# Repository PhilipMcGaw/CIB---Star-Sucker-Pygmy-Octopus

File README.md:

# CIB - Star-Sucker Pygmy Octopus

Programmable load for Fans, Pumps, and Load simulation - Star-Sucker Pygmy Octopus

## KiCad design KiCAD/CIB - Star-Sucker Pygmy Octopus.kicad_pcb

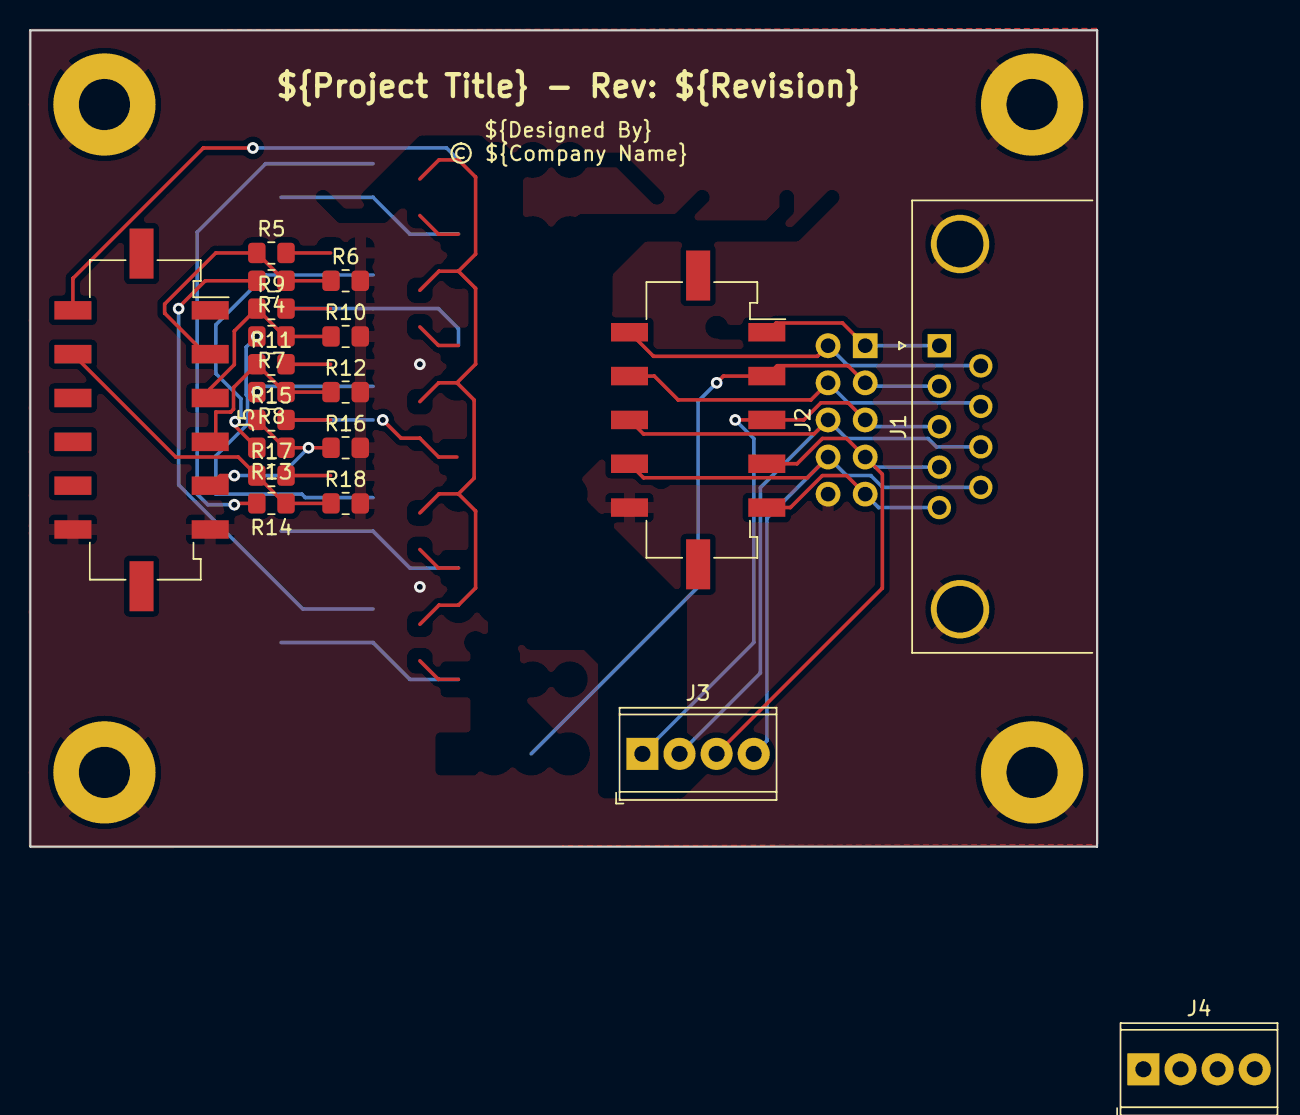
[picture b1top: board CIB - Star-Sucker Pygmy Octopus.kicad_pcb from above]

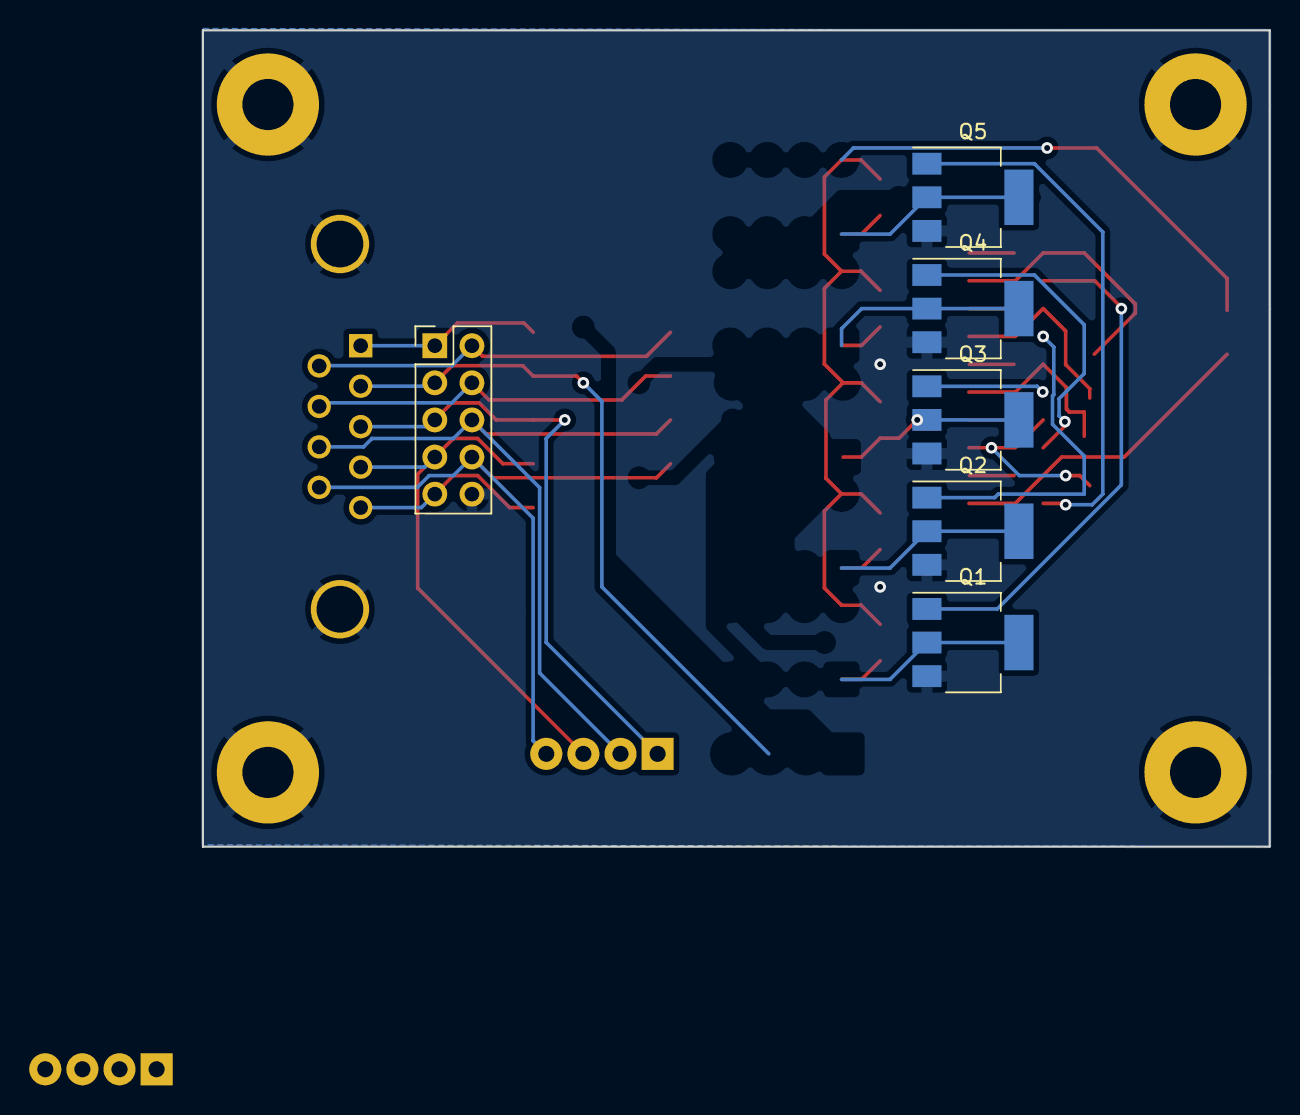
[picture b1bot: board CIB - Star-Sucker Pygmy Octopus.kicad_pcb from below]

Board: 2 copper layers, 73.0 x 55.9 mm, 30 parts (6 on the bottom side), 23 nets.

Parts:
H1, H2, H3, H4: MountingHole; MountingHole_3.5mm_Pad
J1: DA15; DSUB-9_Female_Horizontal_P2.77x2.84mm_EdgePinOffset7.70mm_H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
J2: Molex; Molex_Micro-Fit_3.0_43045-1018_2x05-1MP_P3.00mm_Vertical
J3: PT 3-4; TerminalBlock_Phoenix_MPT-0,5-4-2.54_1x04_P2.54mm_Horizontal
J4: PT 1-2; TerminalBlock_Phoenix_MPT-0,5-4-2.54_1x04_P2.54mm_Horizontal
J5: Enable; Molex_Micro-Fit_3.0_43045-1218_2x06-1MP_P3.00mm_Vertical
J6: Pin Header; PinHeader_2x05_P2.54mm_Vertical
Q1, Q2, Q3, Q4, Q5: Q_NMOS_DGS; SOT-223-3_TabPin2
R4, R10, R12, R18: 0.1; R_0805_2012Metric_Pad1.20x1.40mm_HandSolder
R5, R6, R7, R8, R13, R14, R15, R16: 1k; R_0805_2012Metric_Pad1.20x1.40mm_HandSolder
R9, R11, R17: 500; R_0805_2012Metric_Pad1.20x1.40mm_HandSolder

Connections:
/PT1 in: J1.1, J2.1, J4.1, J6.1
/PT1 out: J1.6, J2.6, J4.2, J6.2
/PT2 in: J1.2, J2.2, J4.3, J6.3
/PT2 out: J1.7, J2.7, J4.4, J6.4
/PT3 in: J1.3, J2.3, J3.1, J6.5
/PT3 out: J1.8, J2.8, J3.2, J6.6
/PT4 in: J1.4, J2.4, J3.3, J6.7
/PT4 out: J1.9, J2.9, J3.4, J6.8
/Pin_05: J1.5, J2.5, J6.9
GND: H1.1 (1_1), H2.1 (1_1), H3.1 (1_1), H4.1 (1_1), J1.0 (PAD), J2.10, J5.6, J5.12, J6.10, R4.2, R10.2, R12.2, R18.2
unnamed: R5.1, R7.1
unnamed: R6.1, R8.1
unnamed: R13.1, R15.1
unnamed: R14.1, R16.1
unnamed: Q1.1 (D), Q3.1 (D), Q5.1 (D)
unnamed: Q1.2 (G), R5.2
unnamed: Q1.3 (S), Q3.3 (S), Q5.3 (S), R9.2, R10.1, R17.2, R18.1
unnamed: Q2.2 (G), R6.2
unnamed: Q3.2 (G), R7.2
unnamed: Q4.2 (G), R8.2
unnamed: Q5.2 (G), R13.2
unnamed: Q2.1 (D), Q4.1 (D)
unnamed: Q2.3 (S), Q4.3 (S), R4.1, R11.2, R12.1
